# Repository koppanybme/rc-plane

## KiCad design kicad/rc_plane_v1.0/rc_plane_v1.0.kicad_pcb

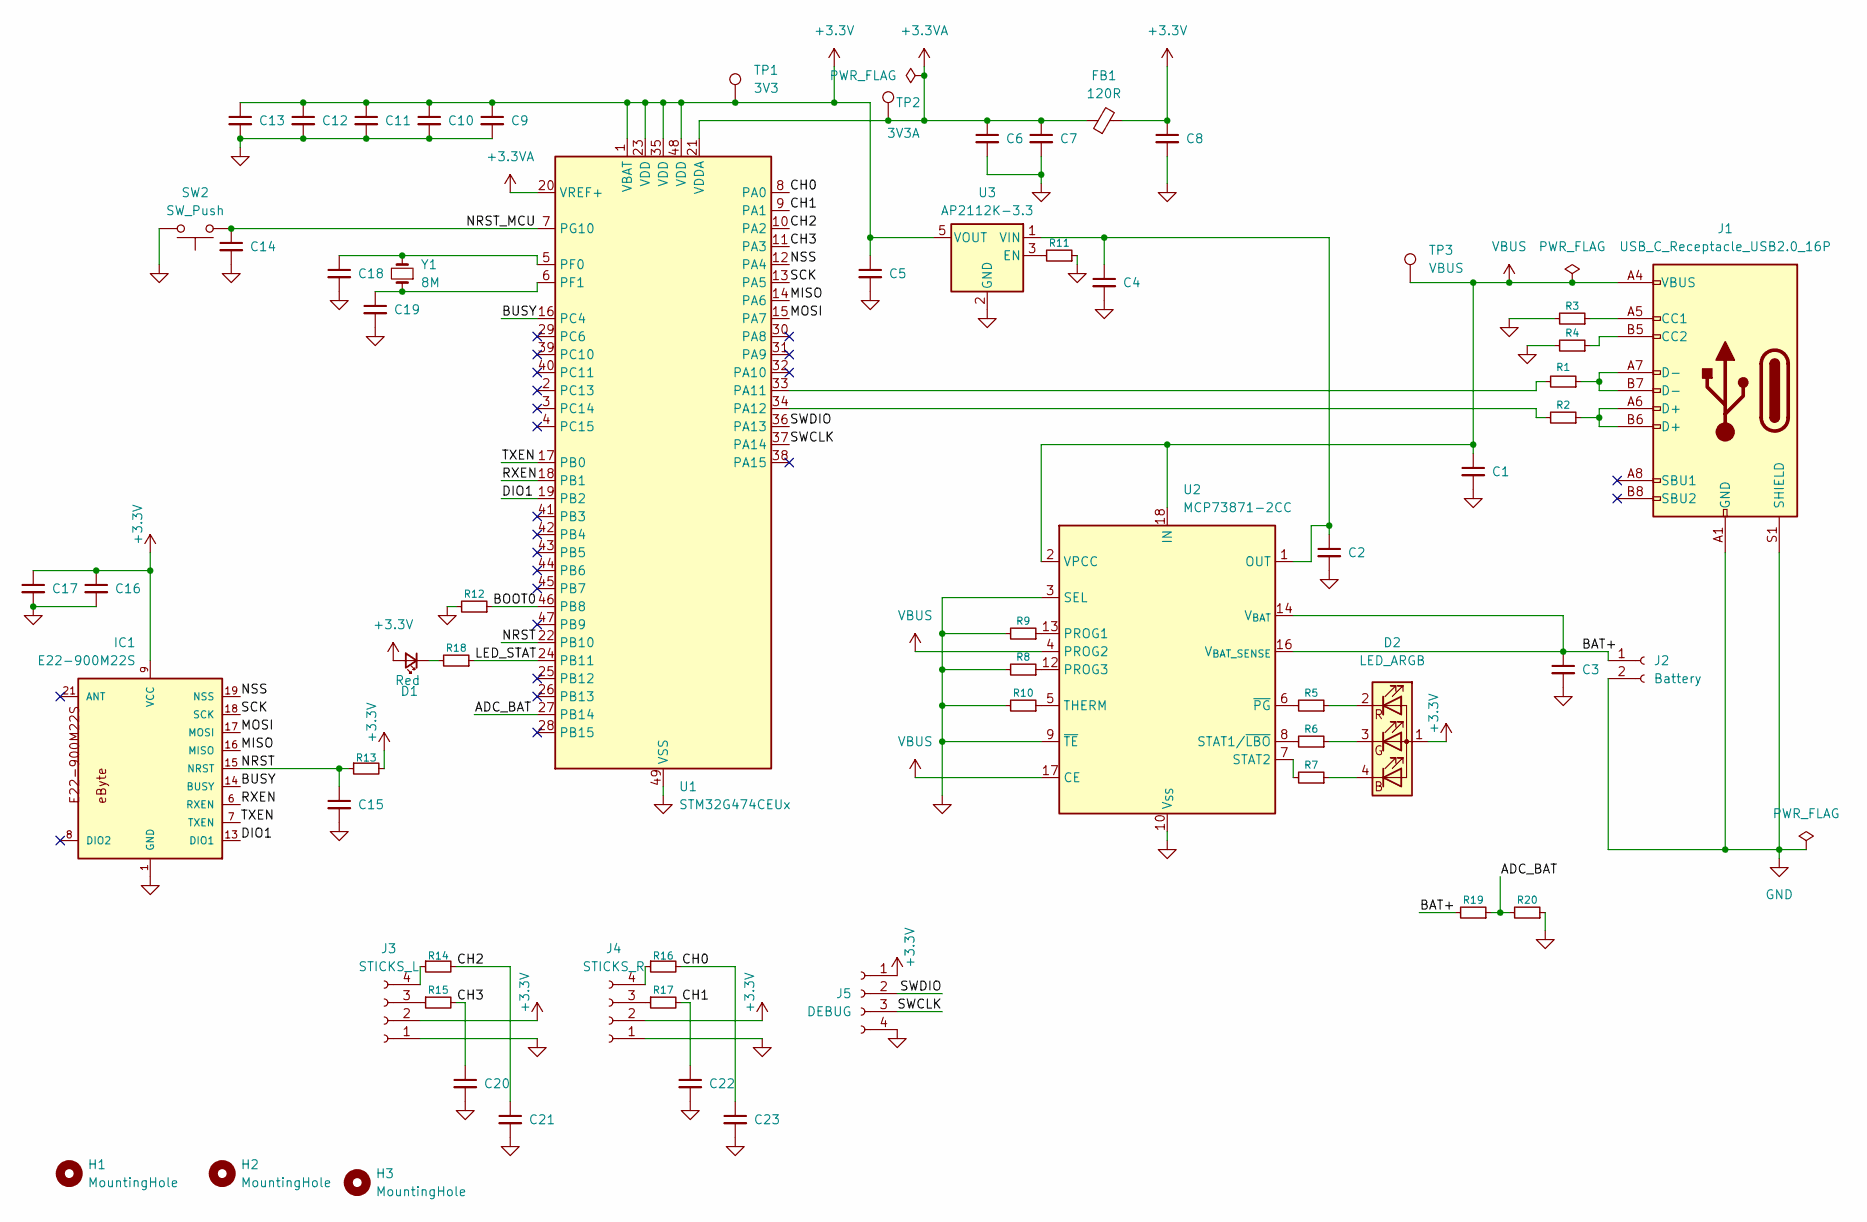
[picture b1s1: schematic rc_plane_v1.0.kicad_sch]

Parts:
C1, C13, C17: 10u; C_0603_1608Metric
C2, C3: 4.7u; C_0603_1608Metric
C4, C5, C7, C8: 1u; C_0603_1608Metric
C6: 10n; C_0603_1608Metric
C9, C10, C11, C12, C14, C15, C16, C20, C21, C22, C23: 100n; C_0603_1608Metric
C18, C19: 15p; C_0603_1608Metric
D1: Red; LED_D3.0mm
D2: LED_ARGB; PinHeader_1x04_P1.27mm_Vertical
FB1: 120R; R_0603_1608Metric
H1, H2, H3: MountingHole; MountingHole_2.2mm_M2
IC1: E22-900M22S
J1: USB_C_Receptacle_USB2.0_16P; USB_C_Receptacle_G-Switch_GT-USB-7010ASV
J2: Battery; JST_GH_SM02B-GHS-TB_1x02-1MP_P1.25mm_Horizontal
J3: STICKS_L; JST_GH_SM04B-GHS-TB_1x04-1MP_P1.25mm_Horizontal
J4: STICKS_R; JST_GH_SM04B-GHS-TB_1x04-1MP_P1.25mm_Horizontal
J5: DEBUG; JST_GH_SM04B-GHS-TB_1x04-1MP_P1.25mm_Horizontal
R1, R2: 22; R_0603_1608Metric
R3, R4: 5.1k; R_0603_1608Metric
R5, R6, R18: 220; R_0603_1608Metric
R7: 18; R_0603_1608Metric
R8: 2k; R_0603_1608Metric
R9: 3.3k; R_0603_1608Metric
R10, R11, R12, R13, R19: 10k; R_0603_1608Metric
R14, R15, R16, R17: 100; R_0603_1608Metric
R20: 24k; R_0603_1608Metric
SW2: SW_Push; SW_Push_6.0_3.5_MPTSM
TP1: 3V3; TestPoint_Pad_D1.0mm
TP2: 3V3A; TestPoint_Pad_D1.0mm
TP3: VBUS; TestPoint_Pad_D1.0mm
U1: STM32G474CEUx; QFN-48-1EP_7x7mm_P0.5mm_EP5.6x5.6mm
U2: MCP73871-2CC; QFN-20-1EP_4x4mm_P0.5mm_EP2.5x2.5mm
U3: AP2112K-3.3; SOT-23-5
Y1: 8M; Crystal_SMD_5032-2Pin_5.0x3.2mm

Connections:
+3.3V: C5.1, C8.1, C9.1, C10.1, C11.1, C12.1, C13.1, C16.1, C17.1, D1.2 (A), D2.1 (A), FB1.2, IC1.9 (VCC), J3.2, J4.2, J5.1, R13.2, TP1.1, U1.1 (VBAT), U1.23 (VDD), U1.35 (VDD), U1.48 (VDD), U3.5 (VOUT)
+3.3VA: C6.1, C7.1, FB1.1, TP2.1, U1.20 (VREF+), U1.21 (VDDA)
/ADC_BAT: R19.1, R20.2, U1.27 (PB14)
/BAT+: C3.1, J2.1, R19.2, U2.14 (V_{BAT}), U2.15 (V_{BAT}), U2.16 (V_{BAT_SENSE})
/BOOT0: R12.1, U1.46 (PB8)
/BUSY: IC1.14 (BUSY), U1.16 (PC4)
/CH0: C23.1, R16.2, U1.8 (PA0)
/CH1: C22.1, R17.2, U1.9 (PA1)
/CH2: C21.1, R14.2, U1.10 (PA2)
/CH3: C20.1, R15.2, U1.11 (PA3)
/DIO1: IC1.13 (DIO1), U1.19 (PB2)
/LED_STAT: R18.1, U1.24 (PB11)
/MISO: IC1.16 (MISO), U1.14 (PA6)
/MOSI: IC1.17 (MOSI), U1.15 (PA7)
/NRST: C15.1, IC1.15 (NRST), R13.1, U1.22 (PB10)
/NRST_MCU: C14.1, SW2.1, U1.7 (PG10)
/NSS: IC1.19 (NSS), U1.12 (PA4)
/RXEN: IC1.6 (RXEN), U1.18 (PB1)
/SCK: IC1.18 (SCK), U1.13 (PA5)
/SWCLK: J5.3, U1.37 (PA14)
/SWDIO: J5.2, U1.36 (PA13)
/TXEN: IC1.7 (TXEN), U1.17 (PB0)
GND: C1.2, C2.2, C3.2, C4.2, C5.2, C6.2, C7.2, C8.2, C9.2, C10.2, C11.2, C12.2, C13.2, C14.2, C15.2, C16.2, C17.2, C18.2, C19.2, C20.2, C21.2, C22.2, C23.2, IC1.1 (GND), IC1.2 (GND), IC1.3 (GND), IC1.4 (GND), IC1.5 (GND), IC1.10 (GND), IC1.11 (GND), IC1.12 (GND), IC1.20 (GND), IC1.22 (GND), J1.A1 (GND), J1.A12 (GND), J1.B1 (GND), J1.B12 (GND), J1.S1 (SHIELD), J2.2, J3.1, J4.1, J5.4, R3.2, R4.2, R8.2, R9.2, R10.2, R11.1, R12.2, R20.1, SW2.2, U1.49 (VSS), U2.3 (SEL), U2.9 (~TE), U2.10 (V_{SS}), U2.11 (V_{SS}), U2.21 (V_{SS}), U3.2 (GND)
unnamed: D1.1 (K), R18.2
unnamed: D2.4 (BK), R7.1
unnamed: D2.3 (GK), R6.1
unnamed: D2.2 (RK), R5.1
unnamed: J1.A5 (CC1), R3.1
unnamed: J1.B5 (CC2), R4.1
unnamed: J1.A6 (D+), J1.B6 (D+), R2.1
unnamed: J1.A7 (D-), J1.B7 (D-), R1.1
unnamed: J3.3, R15.1
unnamed: J3.4, R14.1
unnamed: J4.3, R17.1
unnamed: J4.4, R16.1
unnamed: R1.2, U1.33 (PA11)
unnamed: R2.2, U1.34 (PA12)
unnamed: C18.1, U1.5 (PF0), Y1.2
unnamed: C19.1, U1.6 (PF1), Y1.1
unnamed: R9.1, U2.13 (PROG1)
unnamed: R8.1, U2.12 (PROG3)
unnamed: R6.2, U2.8 (STAT1/~LBO)
unnamed: R7.2, U2.7 (STAT2)
unnamed: R10.1, U2.5 (THERM)
unnamed: R5.2, U2.6 (~PG)
unnamed: R11.2, U3.3 (EN)
unnamed: C2.1, C4.1, U2.1 (OUT), U2.20 (OUT), U3.1 (VIN)
VBUS: C1.1, J1.A4 (VBUS), J1.A9 (VBUS), J1.B4 (VBUS), J1.B9 (VBUS), TP3.1, U2.2 (VPCC), U2.4 (PROG2), U2.17 (CE), U2.18 (IN), U2.19 (IN)

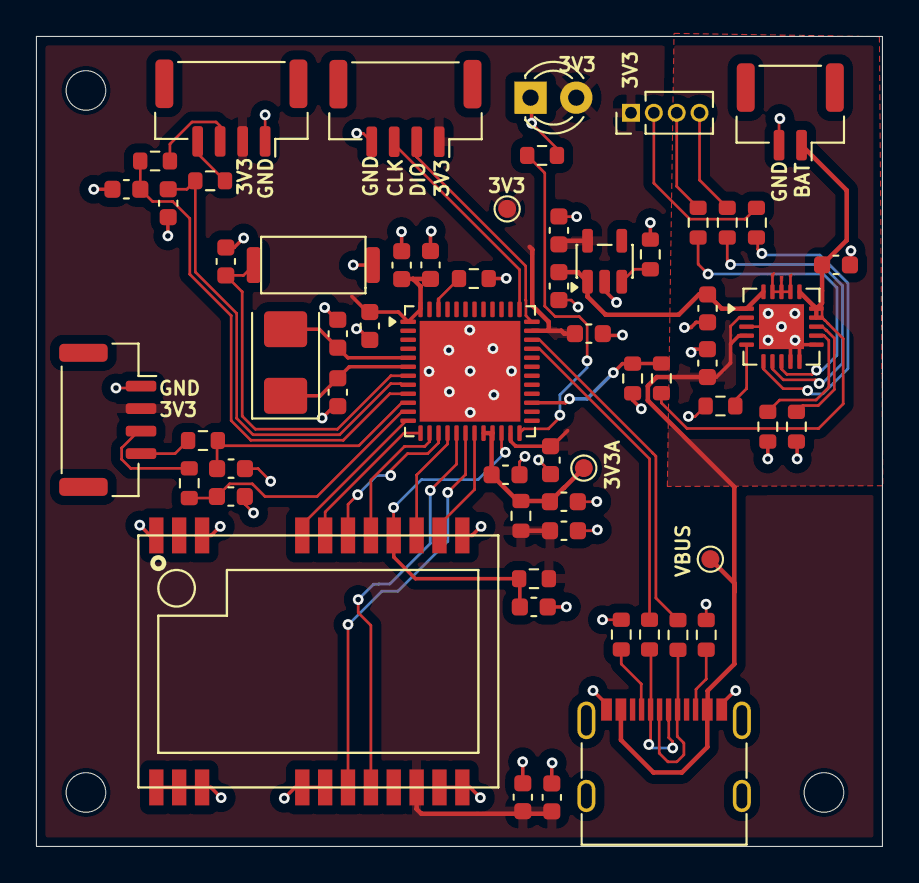
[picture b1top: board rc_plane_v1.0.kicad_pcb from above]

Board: 2 copper layers, 47.0 x 45.0 mm, 63 parts (0 on the bottom side), 48 nets.

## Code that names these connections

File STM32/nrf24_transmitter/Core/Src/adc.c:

/* USER CODE BEGIN Header */
/**
  ******************************************************************************
  * @file    adc.c
  * @brief   This file provides code for the configuration
  *          of the ADC instances.
  ******************************************************************************
  * @attention
  *
  * Copyright (c) 2025 STMicroelectronics.
  * All rights reserved.
  *
  * This software is licensed under terms that can be found in the LICENSE file
  * in the root directory of this software component.
  * If no LICENSE file comes with this software, it is provided AS-IS.
  *
  ******************************************************************************
  */
/* USER CODE END Header */
/* Includes ------------------------------------------------------------------*/
#include "adc.h"

/* USER CODE BEGIN 0 */

/* USER CODE END 0 */

ADC_HandleTypeDef hadc1;
DMA_HandleTypeDef hdma_adc1;

/* ADC1 init function */
void MX_ADC1_Init(void)
{

  /* USER CODE BEGIN ADC1_Init 0 */

  /* USER CODE END ADC1_Init 0 */

  ADC_ChannelConfTypeDef sConfig = {0};

  /* USER CODE BEGIN ADC1_Init 1 */

  /* USER CODE END ADC1_Init 1 */

  /** Common config
  */
  hadc1.Instance = ADC1;
  hadc1.Init.ScanConvMode = ADC_SCAN_ENABLE;
  hadc1.Init.ContinuousConvMode = DISABLE;
  hadc1.Init.DiscontinuousConvMode = DISABLE;
  hadc1.Init.ExternalTrigConv = ADC_EXTERNALTRIGCONV_T2_CC2;
  hadc1.Init.DataAlign = ADC_DATAALIGN_RIGHT;
  hadc1.Init.NbrOfConversion = 4;
  if (HAL_ADC_Init(&hadc1) != HAL_OK)
  {
    Error_Handler();
  }

  /** Configure Regular Channel
  */
  sConfig.Channel = ADC_CHANNEL_0;
  sConfig.Rank = ADC_REGULAR_RANK_1;
  sConfig.SamplingTime = ADC_SAMPLETIME_28CYCLES_5;
  if (HAL_ADC_ConfigChannel(&hadc1, &sConfig) != HAL_OK)
  {
    Error_Handler();
  }

  /** Configure Regular Channel
  */
  sConfig.Channel = ADC_CHANNEL_1;
  sConfig.Rank = ADC_REGULAR_RANK_2;
  if (HAL_ADC_ConfigChannel(&hadc1, &sConfig) != HAL_OK)
  {
    Error_Handler();
  }

  /** Configure Regular Channel
  */
  sConfig.Channel = ADC_CHANNEL_2;
  sConfig.Rank = ADC_REGULAR_RANK_3;
  if (HAL_ADC_ConfigChannel(&hadc1, &sConfig) != HAL_OK)
  {
    Error_Handler();
  }

  /** Configure Regular Channel
  */
  sConfig.Channel = ADC_CHANNEL_3;
  sConfig.Rank = ADC_REGULAR_RANK_4;
  if (HAL_ADC_ConfigChannel(&hadc1, &sConfig) != HAL_OK)
  {
    Error_Handler();
  }
  /* USER CODE BEGIN ADC1_Init 2 */

  /* USER CODE END ADC1_Init 2 */

}

void HAL_ADC_MspInit(ADC_HandleTypeDef* adcHandle)
{

  GPIO_InitTypeDef GPIO_InitStruct = {0};
  if(adcHandle->Instance==ADC1)
  {
  /* USER CODE BEGIN ADC1_MspInit 0 */

  /* USER CODE END ADC1_MspInit 0 */
    /* ADC1 clock enable */
    __HAL_RCC_ADC1_CLK_ENABLE();

    __HAL_RCC_GPIOA_CLK_ENABLE();
    /**ADC1 GPIO Configuration
    PA0-WKUP     ------> ADC1_IN0
    PA1     ------> ADC1_IN1
    PA2     ------> ADC1_IN2
    PA3     ------> ADC1_IN3
    */
    GPIO_InitStruct.Pin = GPIO_PIN_0|GPIO_PIN_1|GPIO_PIN_2|GPIO_PIN_3;
    GPIO_InitStruct.Mode = GPIO_MODE_ANALOG;
    HAL_GPIO_Init(GPIOA, &GPIO_InitStruct);

    /* ADC1 DMA Init */
    /* ADC1 Init */
    hdma_adc1.Instance = DMA1_Channel1;
    hdma_adc1.Init.Direction = DMA_PERIPH_TO_MEMORY;
    hdma_adc1.Init.PeriphInc = DMA_PINC_DISABLE;
    hdma_adc1.Init.MemInc = DMA_MINC_ENABLE;
    hdma_adc1.Init.PeriphDataAlignment = DMA_PDATAALIGN_WORD;
    hdma_adc1.Init.MemDataAlignment = DMA_MDATAALIGN_WORD;
    hdma_adc1.Init.Mode = DMA_CIRCULAR;
    hdma_adc1.Init.Priority = DMA_PRIORITY_LOW;
    if (HAL_DMA_Init(&hdma_adc1) != HAL_OK)
    {
      Error_Handler();
    }

    __HAL_LINKDMA(adcHandle,DMA_Handle,hdma_adc1);

  /* USER CODE BEGIN ADC1_MspInit 1 */

  /* USER CODE END ADC1_MspInit 1 */
  }
}

void HAL_ADC_MspDeInit(ADC_HandleTypeDef* adcHandle)
{

  if(adcHandle->Instance==ADC1)
  {
  /* USER CODE BEGIN ADC1_MspDeInit 0 */

  /* USER CODE END ADC1_MspDeInit 0 */
    /* Peripheral clock disable */
    __HAL_RCC_ADC1_CLK_DISABLE();

    /**ADC1 GPIO Configuration
    PA0-WKUP     ------> ADC1_IN0
    PA1     ------> ADC1_IN1
    PA2     ------> ADC1_IN2
    PA3     ------> ADC1_IN3
    */
    HAL_GPIO_DeInit(GPIOA, GPIO_PIN_0|GPIO_PIN_1|GPIO_PIN_2|GPIO_PIN_3);

    /* ADC1 DMA DeInit */
    HAL_DMA_DeInit(adcHandle->DMA_Handle);
  /* USER CODE BEGIN ADC1_MspDeInit 1 */

  /* USER CODE END ADC1_MspDeInit 1 */
  }
}

/* USER CODE BEGIN 1 */

/* USER CODE END 1 */

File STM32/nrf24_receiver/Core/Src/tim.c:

/* USER CODE BEGIN Header */
/**
  ******************************************************************************
  * @file    tim.c
  * @brief   This file provides code for the configuration
  *          of the TIM instances.
  ******************************************************************************
  * @attention
  *
  * Copyright (c) 2025 STMicroelectronics.
  * All rights reserved.
  *
  * This software is licensed under terms that can be found in the LICENSE file
  * in the root directory of this software component.
  * If no LICENSE file comes with this software, it is provided AS-IS.
  *
  ******************************************************************************
  */
/* USER CODE END Header */
/* Includes ------------------------------------------------------------------*/
#include "tim.h"

/* USER CODE BEGIN 0 */

/* USER CODE END 0 */

TIM_HandleTypeDef htim2;
TIM_HandleTypeDef htim3;

/* TIM2 init function */
void MX_TIM2_Init(void)
{

  /* USER CODE BEGIN TIM2_Init 0 */

  /* USER CODE END TIM2_Init 0 */

  TIM_ClockConfigTypeDef sClockSourceConfig = {0};
  TIM_MasterConfigTypeDef sMasterConfig = {0};

  /* USER CODE BEGIN TIM2_Init 1 */

  /* USER CODE END TIM2_Init 1 */
  htim2.Instance = TIM2;
  htim2.Init.Prescaler = 72-1;
  htim2.Init.CounterMode = TIM_COUNTERMODE_UP;
  htim2.Init.Period = 4000-1;
  htim2.Init.ClockDivision = TIM_CLOCKDIVISION_DIV1;
  htim2.Init.AutoReloadPreload = TIM_AUTORELOAD_PRELOAD_DISABLE;
  if (HAL_TIM_Base_Init(&htim2) != HAL_OK)
  {
    Error_Handler();
  }
  sClockSourceConfig.ClockSource = TIM_CLOCKSOURCE_INTERNAL;
  if (HAL_TIM_ConfigClockSource(&htim2, &sClockSourceConfig) != HAL_OK)
  {
    Error_Handler();
  }
  sMasterConfig.MasterOutputTrigger = TIM_TRGO_RESET;
  sMasterConfig.MasterSlaveMode = TIM_MASTERSLAVEMODE_DISABLE;
  if (HAL_TIMEx_MasterConfigSynchronization(&htim2, &sMasterConfig) != HAL_OK)
  {
    Error_Handler();
  }
  /* USER CODE BEGIN TIM2_Init 2 */

  /* USER CODE END TIM2_Init 2 */

}
/* TIM3 init function */
void MX_TIM3_Init(void)
{

  /* USER CODE BEGIN TIM3_Init 0 */

  /* USER CODE END TIM3_Init 0 */

  TIM_MasterConfigTypeDef sMasterConfig = {0};
  TIM_OC_InitTypeDef sConfigOC = {0};

  /* USER CODE BEGIN TIM3_Init 1 */

  /* USER CODE END TIM3_Init 1 */
  htim3.Instance = TIM3;
  htim3.Init.Prescaler = 72-1;
  htim3.Init.CounterMode = TIM_COUNTERMODE_UP;
  htim3.Init.Period = 20000-1;
  htim3.Init.ClockDivision = TIM_CLOCKDIVISION_DIV1;
  htim3.Init.AutoReloadPreload = TIM_AUTORELOAD_PRELOAD_DISABLE;
  if (HAL_TIM_PWM_Init(&htim3) != HAL_OK)
  {
    Error_Handler();
  }
  sMasterConfig.MasterOutputTrigger = TIM_TRGO_RESET;
  sMasterConfig.MasterSlaveMode = TIM_MASTERSLAVEMODE_DISABLE;
  if (HAL_TIMEx_MasterConfigSynchronization(&htim3, &sMasterConfig) != HAL_OK)
  {
    Error_Handler();
  }
  sConfigOC.OCMode = TIM_OCMODE_PWM1;
  sConfigOC.Pulse = 0;
  sConfigOC.OCPolarity = TIM_OCPOLARITY_HIGH;
  sConfigOC.OCFastMode = TIM_OCFAST_DISABLE;
  if (HAL_TIM_PWM_ConfigChannel(&htim3, &sConfigOC, TIM_CHANNEL_1) != HAL_OK)
  {
    Error_Handler();
  }
  if (HAL_TIM_PWM_ConfigChannel(&htim3, &sConfigOC, TIM_CHANNEL_2) != HAL_OK)
  {
    Error_Handler();
  }
  if (HAL_TIM_PWM_ConfigChannel(&htim3, &sConfigOC, TIM_CHANNEL_3) != HAL_OK)
  {
    Error_Handler();
  }
  if (HAL_TIM_PWM_ConfigChannel(&htim3, &sConfigOC, TIM_CHANNEL_4) != HAL_OK)
  {
    Error_Handler();
  }
  /* USER CODE BEGIN TIM3_Init 2 */

  /* USER CODE END TIM3_Init 2 */
  HAL_TIM_MspPostInit(&htim3);

}

void HAL_TIM_Base_MspInit(TIM_HandleTypeDef* tim_baseHandle)
{

  if(tim_baseHandle->Instance==TIM2)
  {
  /* USER CODE BEGIN TIM2_MspInit 0 */

  /* USER CODE END TIM2_MspInit 0 */
    /* TIM2 clock enable */
    __HAL_RCC_TIM2_CLK_ENABLE();

    /* TIM2 interrupt Init */
    HAL_NVIC_SetPriority(TIM2_IRQn, 0, 0);
    HAL_NVIC_EnableIRQ(TIM2_IRQn);
  /* USER CODE BEGIN TIM2_MspInit 1 */

  /* USER CODE END TIM2_MspInit 1 */
  }
}

void HAL_TIM_PWM_MspInit(TIM_HandleTypeDef* tim_pwmHandle)
{

  if(tim_pwmHandle->Instance==TIM3)
  {
  /* USER CODE BEGIN TIM3_MspInit 0 */

  /* USER CODE END TIM3_MspInit 0 */
    /* TIM3 clock enable */
    __HAL_RCC_TIM3_CLK_ENABLE();

    /* TIM3 interrupt Init */
    HAL_NVIC_SetPriority(TIM3_IRQn, 0, 0);
    HAL_NVIC_EnableIRQ(TIM3_IRQn);
  /* USER CODE BEGIN TIM3_MspInit 1 */

  /* USER CODE END TIM3_MspInit 1 */
  }
}
void HAL_TIM_MspPostInit(TIM_HandleTypeDef* timHandle)
{

  GPIO_InitTypeDef GPIO_InitStruct = {0};
  if(timHandle->Instance==TIM3)
  {
  /* USER CODE BEGIN TIM3_MspPostInit 0 */

  /* USER CODE END TIM3_MspPostInit 0 */

    __HAL_RCC_GPIOA_CLK_ENABLE();
    __HAL_RCC_GPIOB_CLK_ENABLE();
    /**TIM3 GPIO Configuration
    PA6     ------> TIM3_CH1
    PA7     ------> TIM3_CH2
    PB0     ------> TIM3_CH3
    PB1     ------> TIM3_CH4
    */
    GPIO_InitStruct.Pin = GPIO_PIN_6|GPIO_PIN_7;
    GPIO_InitStruct.Mode = GPIO_MODE_AF_PP;
    GPIO_InitStruct.Speed = GPIO_SPEED_FREQ_LOW;
    HAL_GPIO_Init(GPIOA, &GPIO_InitStruct);

    GPIO_InitStruct.Pin = GPIO_PIN_0|GPIO_PIN_1;
    GPIO_InitStruct.Mode = GPIO_MODE_AF_PP;
    GPIO_InitStruct.Speed = GPIO_SPEED_FREQ_LOW;
    HAL_GPIO_Init(GPIOB, &GPIO_InitStruct);

  /* USER CODE BEGIN TIM3_MspPostInit 1 */

  /* USER CODE END TIM3_MspPostInit 1 */
  }

}

void HAL_TIM_Base_MspDeInit(TIM_HandleTypeDef* tim_baseHandle)
{

  if(tim_baseHandle->Instance==TIM2)
  {
  /* USER CODE BEGIN TIM2_MspDeInit 0 */

  /* USER CODE END TIM2_MspDeInit 0 */
    /* Peripheral clock disable */
    __HAL_RCC_TIM2_CLK_DISABLE();

    /* TIM2 interrupt Deinit */
    HAL_NVIC_DisableIRQ(TIM2_IRQn);
  /* USER CODE BEGIN TIM2_MspDeInit 1 */

  /* USER CODE END TIM2_MspDeInit 1 */
  }
}

void HAL_TIM_PWM_MspDeInit(TIM_HandleTypeDef* tim_pwmHandle)
{

  if(tim_pwmHandle->Instance==TIM3)
  {
  /* USER CODE BEGIN TIM3_MspDeInit 0 */

  /* USER CODE END TIM3_MspDeInit 0 */
    /* Peripheral clock disable */
    __HAL_RCC_TIM3_CLK_DISABLE();

    /* TIM3 interrupt Deinit */
    HAL_NVIC_DisableIRQ(TIM3_IRQn);
  /* USER CODE BEGIN TIM3_MspDeInit 1 */

  /* USER CODE END TIM3_MspDeInit 1 */
  }
}

/* USER CODE BEGIN 1 */

/* USER CODE END 1 */

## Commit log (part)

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2025-04-15 Example of bi-dircetional communication
    Data rate test of ack payloads
2025-04-20 Ack payload speed test
2025-04-21 Receiver test update
    10m 150 RT/s
2025-04-21 Transmitter test update
    Test for sent, received, loss rate
2025-05-01 Can communicate 400 ACK/sec
2025-07-17 transmitter lcd working, typo fix
2025-08-02 Added videos of maiden flight
2025-08-02 Added images of transmitter
2025-09-13 Added NRF24 driver for STM32 //TODO async spi, implement all radio commands
2025-09-17 implemented 4 channel servo control //TODO async spi, two-way communication
2025-11-13 Implemented joystick calibration Implemented signal lost behaviour
